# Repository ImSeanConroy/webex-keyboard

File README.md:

# webex-keyboard

Custom mini keypad designed to act as a Webex controller making it easily to toggle audio and video whilst on calls. Future versions will resolve minor issues, have more keys and an improved PCB design, potentially moving away from pre-built development boards to further reduce the keypads overall footprint.

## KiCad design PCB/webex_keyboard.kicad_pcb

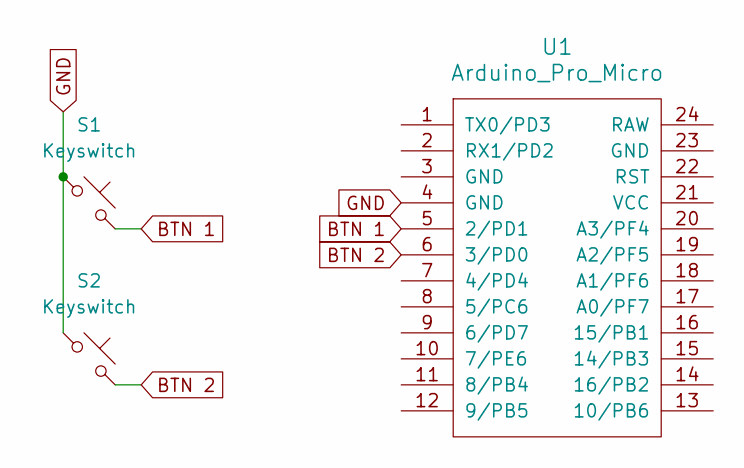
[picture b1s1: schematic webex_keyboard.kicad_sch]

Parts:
S1, S2: Keyswitch; MX_PCB_1.00u
U1: Arduino_Pro_Micro

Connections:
BTN 1: S1.2, U1.5 (2/PD1)
BTN 2: S2.2, U1.6 (3/PD0)
GND: S1.1, S2.1, U1.4 (GND)

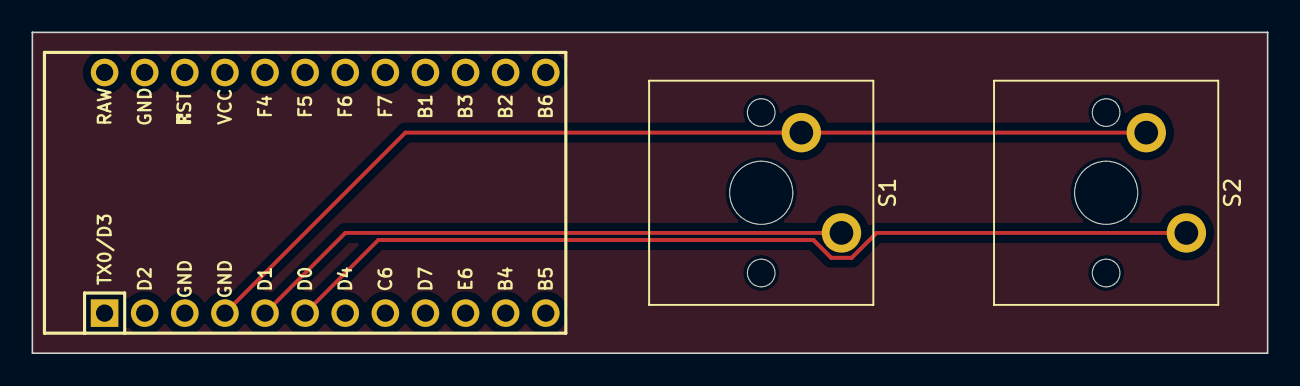
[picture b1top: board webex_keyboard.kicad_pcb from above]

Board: 2 copper layers, 78.2 x 20.3 mm, 3 parts (0 on the bottom side), 3 nets.

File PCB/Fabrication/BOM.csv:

"Id";"Designator";"Footprint";"Quantity";"Designation";"Supplier and ref";
1;"S2,S1";"MX_PCB_1.00u";2;"Keyswitch";;;
2;"U1";"Arduino_Pro_Micro";1;"Arduino_Pro_Micro";;;

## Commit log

2024-02-04 Create basic mini keyboard script
2024-02-04 Add debounce
2024-02-17 Add v1 pcb design files
2024-02-25 Add case stl files
2024-02-25 Refactor firmware
2024-03-03 Add video examples
